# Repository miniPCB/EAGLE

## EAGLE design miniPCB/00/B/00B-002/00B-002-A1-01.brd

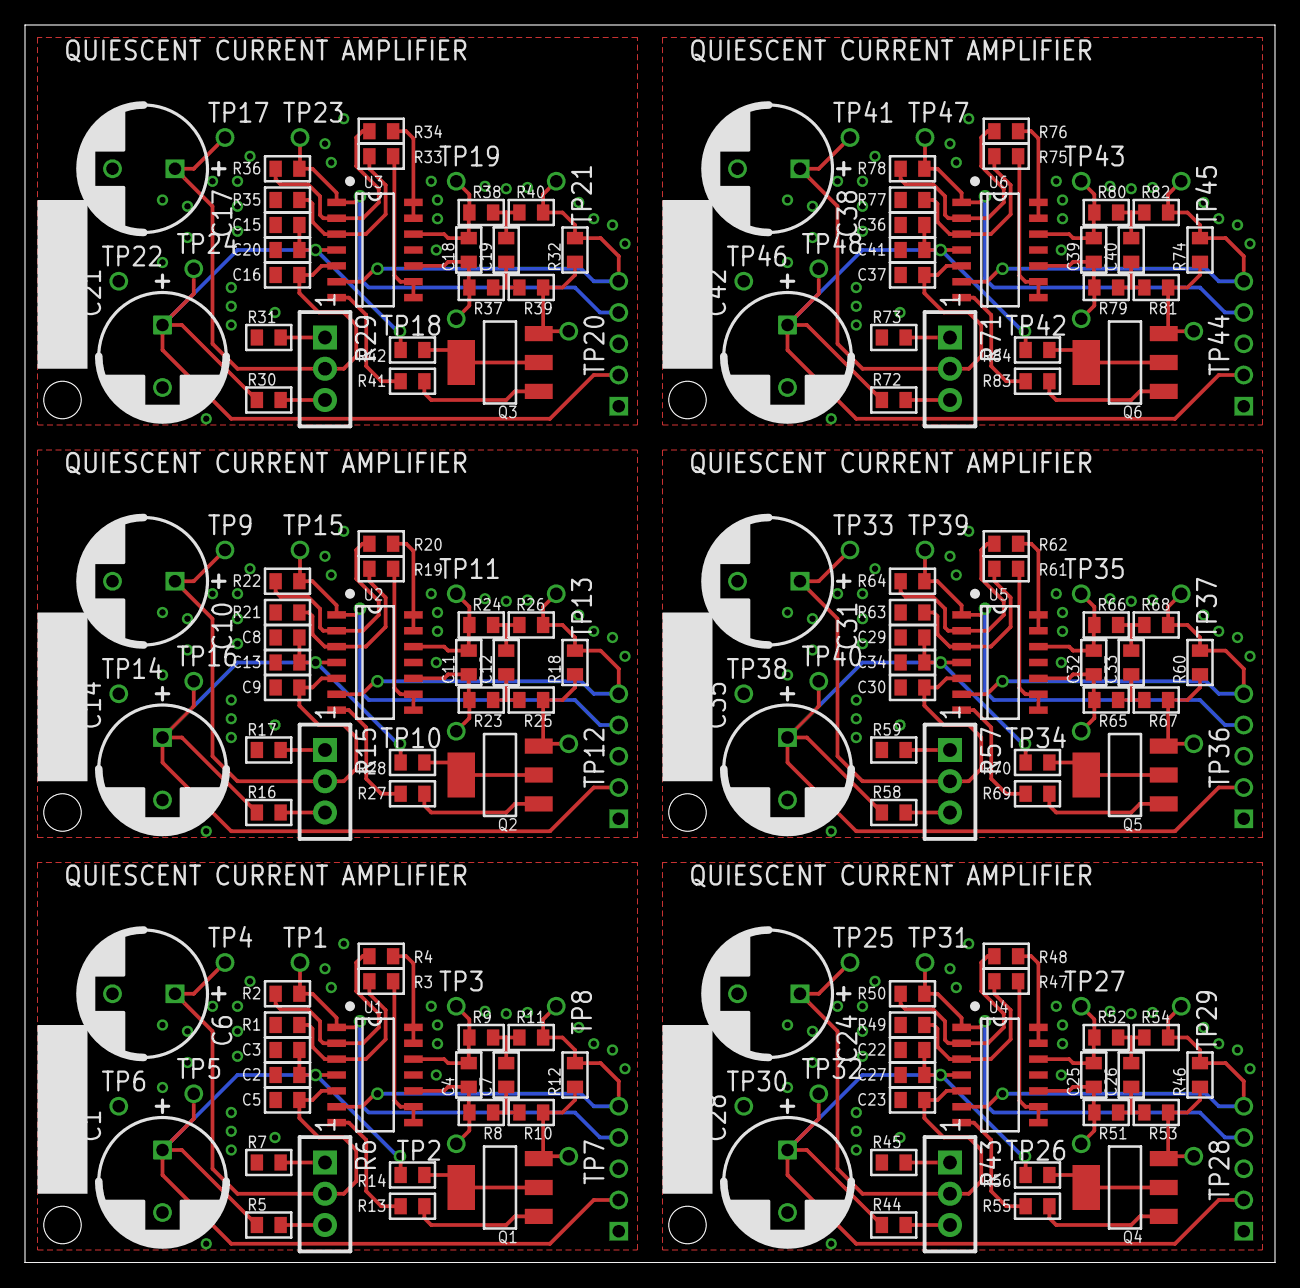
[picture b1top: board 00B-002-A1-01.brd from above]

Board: 2 copper layers, 100.0 x 99.0 mm, 198 parts (0 on the bottom side), 114 nets.

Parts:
C1, C14, C21, C28, C35, C42: 1u; C5MM
C2, C3, C8, C13, C15, C20, C22, C27, C29, C34, C36, C41: 1u; C0805
C4, C5, C7, C9, C11, C12, C16, C18, C19, C23, C25, C26, C30, C32, C33, C37, C39, C40: C0805
C6, C10, C17, C24, C31, C38: C5MM
P1, P2, P3, P4, P5, P6: PINS_1X5
PCB1, PCB2, PCB3, PCB4, PCB5, PCB6: MINIPCB_0P_33X50
Q1, Q2, Q3, Q4, Q5, Q6: SOT223
R1, R2, R3, R4, R5, R7, R8, R9, R10, R11, R12, R13, R14, R16, R17, R18, R19, R20, R21, R22, R23, R24, R25, R26, R27, R28, R30, R31, R32, R33, R34, R35, R36, R37, R38, R39, R40, R41, R42, R44, R45, R46, R47, R48, R49, R50, R51, R52, R53, R54, R55, R56, R58, R59, R60, R61, R62, R63, R64, R65, R66, R67, R68, R69, R70, R72, R73, R74, R75, R76, R77, R78, R79, R80, R81, R82, R83, R84: R0805
R6, R15, R29, R43, R57, R71: TRIM_0100
TP1, TP2, TP3, TP4, TP5, TP6, TP7, TP8, TP9, TP10, TP11, TP12, TP13, TP14, TP15, TP16, TP17, TP18, TP19, TP20, TP21, TP22, TP23, TP24, TP25, TP26, TP27, TP28, TP29, TP30, TP31, TP32, TP33, TP34, TP35, TP36, TP37, TP38, TP39, TP40, TP41, TP42, TP43, TP44, TP45, TP46, TP47, TP48: PINS_1_TESTPOINT_KE5000_NOTEXT
U1, U2, U3, U4, U5, U6: 324; SO14

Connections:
GND: C1.-, C2.2, C3.2, C5.2, C6.-, P1.1, R1.2, R7.1, TP6.1, U1.11
GND1: C8.2, C9.2, C10.-, C13.2, C14.-, P2.1, R17.1, R21.2, TP14.1, U2.11
GND2: C15.2, C16.2, C17.-, C20.2, C21.-, P3.1, R31.1, R35.2, TP22.1, U3.11
GND3: C22.2, C23.2, C24.-, C27.2, C28.-, P4.1, R45.1, R49.2, TP30.1, U4.11
GND4: C29.2, C30.2, C31.-, C34.2, C35.-, P5.1, R59.1, R63.2, TP38.1, U5.11
GND5: C36.2, C37.2, C38.-, C41.2, C42.-, P6.1, R73.1, R77.2, TP46.1, U6.11
ISIGNAL: P1.4, R2.2, TP1.1, U1.1
ISIGNAL1: P2.4, R22.2, TP15.1, U2.1
ISIGNAL2: P3.4, R36.2, TP23.1, U3.1
ISIGNAL3: P4.4, R50.2, TP31.1, U4.1
ISIGNAL4: P5.4, R64.2, TP39.1, U5.1
ISIGNAL5: P6.4, R78.2, TP47.1, U6.1
unnamed: Q1.2, Q1.4.TAB, R14.1
unnamed: R3.1, U1.8, U1.9
unnamed: R4.1, U1.13, U1.14
unnamed: Q1.1, R13.2
unnamed: R6.1, R7.2
unnamed: R5.1, R6.3
unnamed: R13.1, U1.7
unnamed: R2.1, R4.2, U1.2
unnamed: R1.1, R3.2, U1.3
unnamed: R15.1, R17.2
unnamed: R15.3, R16.1
unnamed: R19.1, U2.8, U2.9
unnamed: R20.1, U2.13, U2.14
unnamed: C4.1, R8.2, TP2.1, U1.10
unnamed: C4.2, R9.2, TP3.1, U1.12
unnamed: C7.1, R8.1, R10.2
unnamed: C7.2, R9.1, R11.2
unnamed: R20.2, R22.1, U2.2
unnamed: R19.2, R21.1, U2.3
unnamed: C11.1, R23.2, TP10.1, U2.10
unnamed: C11.2, R24.2, TP11.1, U2.12
unnamed: C12.1, R23.1, R25.2
unnamed: C12.2, R24.1, R26.2
unnamed: Q2.1, R27.2
unnamed: R27.1, U2.7
unnamed: Q2.2, Q2.4.TAB, R28.1
unnamed: R29.1, R31.2
unnamed: R29.3, R30.1
unnamed: R33.1, U3.8, U3.9
unnamed: R34.1, U3.13, U3.14
unnamed: R34.2, R36.1, U3.2
unnamed: R33.2, R35.1, U3.3
unnamed: C18.1, R37.2, TP18.1, U3.10
unnamed: C18.2, R38.2, TP19.1, U3.12
unnamed: C19.1, R37.1, R39.2
unnamed: C19.2, R38.1, R40.2
unnamed: Q3.1, R41.2
unnamed: R41.1, U3.7
unnamed: Q3.2, Q3.4.TAB, R42.1
unnamed: R43.1, R45.2
unnamed: R43.3, R44.1
unnamed: R47.1, U4.8, U4.9
unnamed: R48.1, U4.13, U4.14
unnamed: R48.2, R50.1, U4.2
unnamed: R47.2, R49.1, U4.3
unnamed: C25.1, R51.2, TP26.1, U4.10
unnamed: C25.2, R52.2, TP27.1, U4.12
unnamed: C26.1, R51.1, R53.2
unnamed: C26.2, R52.1, R54.2
unnamed: Q4.1, R55.2
unnamed: R55.1, U4.7
unnamed: Q4.2, Q4.4.TAB, R56.1
unnamed: R57.1, R59.2
unnamed: R57.3, R58.1
unnamed: R61.1, U5.8, U5.9
unnamed: R62.1, U5.13, U5.14
unnamed: R62.2, R64.1, U5.2
unnamed: R61.2, R63.1, U5.3
unnamed: C32.1, R65.2, TP34.1, U5.10
unnamed: C32.2, R66.2, TP35.1, U5.12
unnamed: C33.1, R65.1, R67.2
unnamed: C33.2, R66.1, R68.2
unnamed: Q5.1, R69.2
unnamed: R69.1, U5.7
unnamed: Q5.2, Q5.4.TAB, R70.1
unnamed: R71.1, R73.2
unnamed: R71.3, R72.1
unnamed: R75.1, U6.8, U6.9
unnamed: R76.1, U6.13, U6.14
unnamed: R76.2, R78.1, U6.2
unnamed: R75.2, R77.1, U6.3
unnamed: C39.1, R79.2, TP42.1, U6.10
unnamed: C39.2, R80.2, TP43.1, U6.12
unnamed: C40.1, R79.1, R81.2
unnamed: C40.2, R80.1, R82.2
unnamed: Q6.1, R83.2
unnamed: R83.1, U6.7
unnamed: Q6.2, Q6.4.TAB, R84.1
V+: C1.+, C2.1, C3.1, P1.2, R5.2, R14.2, TP5.1, U1.4
V+1: C8.1, C13.1, C14.+, P2.2, R16.2, R28.2, TP16.1, U2.4
V+2: C15.1, C20.1, C21.+, P3.2, R30.2, R42.2, TP24.1, U3.4
V+3: C22.1, C27.1, C28.+, P4.2, R44.2, R56.2, TP32.1, U4.4
V+4: C29.1, C34.1, C35.+, P5.2, R58.2, R70.2, TP40.1, U5.4
V+5: C36.1, C41.1, C42.+, P6.2, R72.2, R84.2, TP48.1, U6.4
VOUT: P1.5, R11.1, R12.2, TP8.1, U1.6
VOUT1: P2.5, R18.2, R26.1, TP13.1, U2.6
VOUT2: P3.5, R32.2, R40.1, TP21.1, U3.6
VOUT3: P4.5, R46.2, R54.1, TP29.1, U4.6
VOUT4: P5.5, R60.2, R68.1, TP37.1, U5.6
VOUT5: P6.5, R74.2, R82.1, TP45.1, U6.6
VREF: C5.1, C6.+, R6.2, TP4.1, U1.5
VREF1: C9.1, C10.+, R15.2, TP9.1, U2.5
VREF2: C16.1, C17.+, R29.2, TP17.1, U3.5
VREF3: C23.1, C24.+, R43.2, TP25.1, U4.5
VREF4: C30.1, C31.+, R57.2, TP33.1, U5.5
VREF5: C37.1, C38.+, R71.2, TP41.1, U6.5
VSIGAL: Q1.3, R10.1, R12.1, TP7.1
VSIGAL1: Q2.3, R18.1, R25.1, TP12.1
VSIGAL2: Q3.3, R32.1, R39.1, TP20.1
VSIGAL3: Q4.3, R46.1, R53.1, TP28.1
VSIGAL4: Q5.3, R60.1, R67.1, TP36.1
VSIGAL5: Q6.3, R74.1, R81.1, TP44.1

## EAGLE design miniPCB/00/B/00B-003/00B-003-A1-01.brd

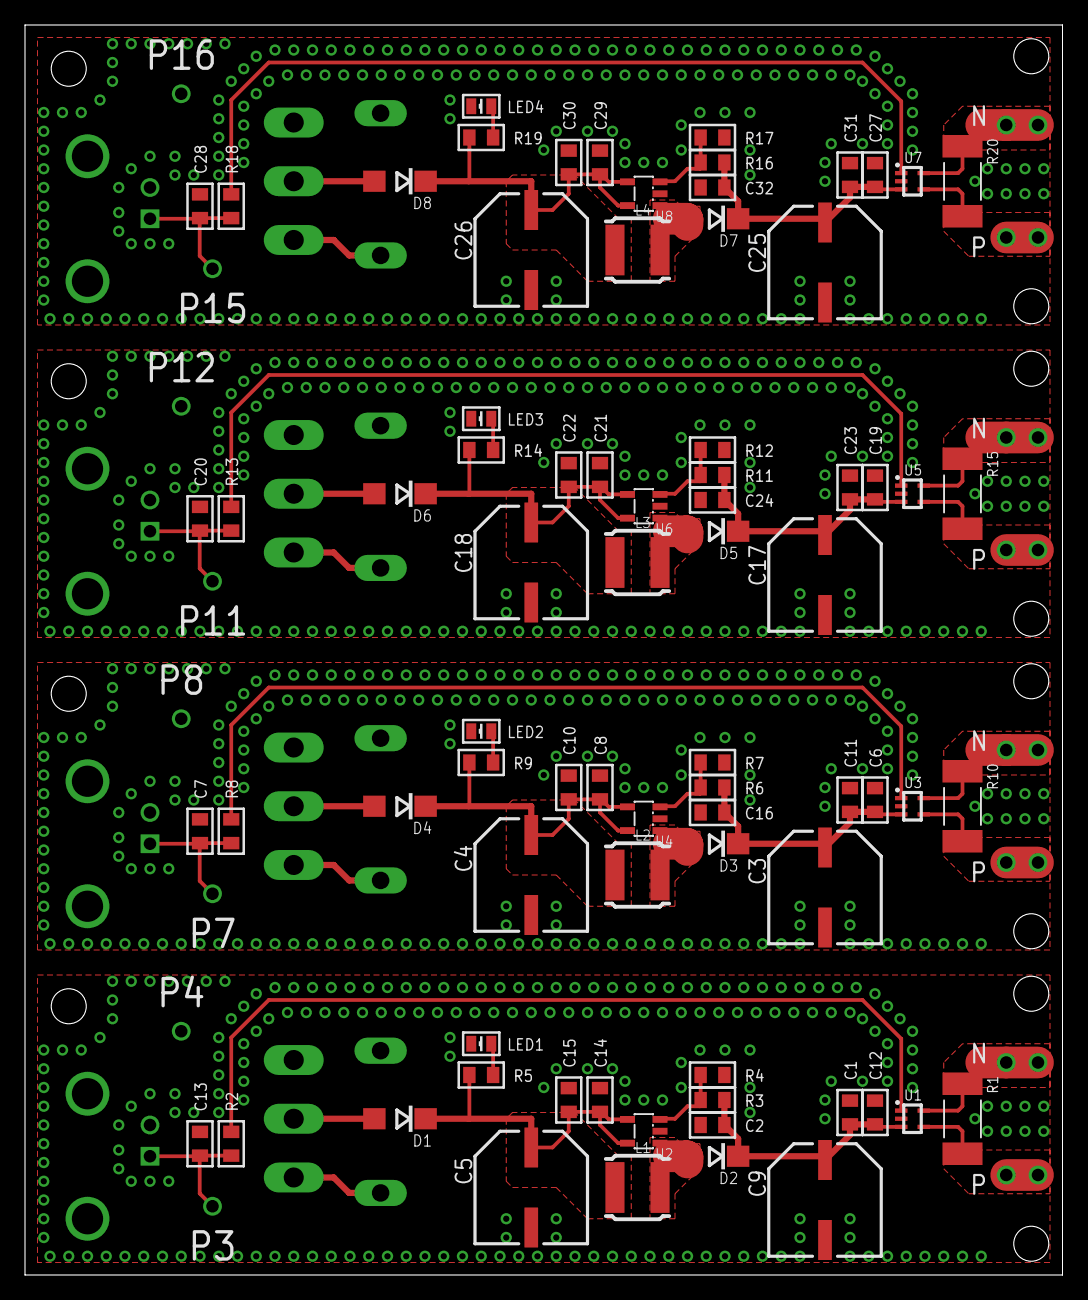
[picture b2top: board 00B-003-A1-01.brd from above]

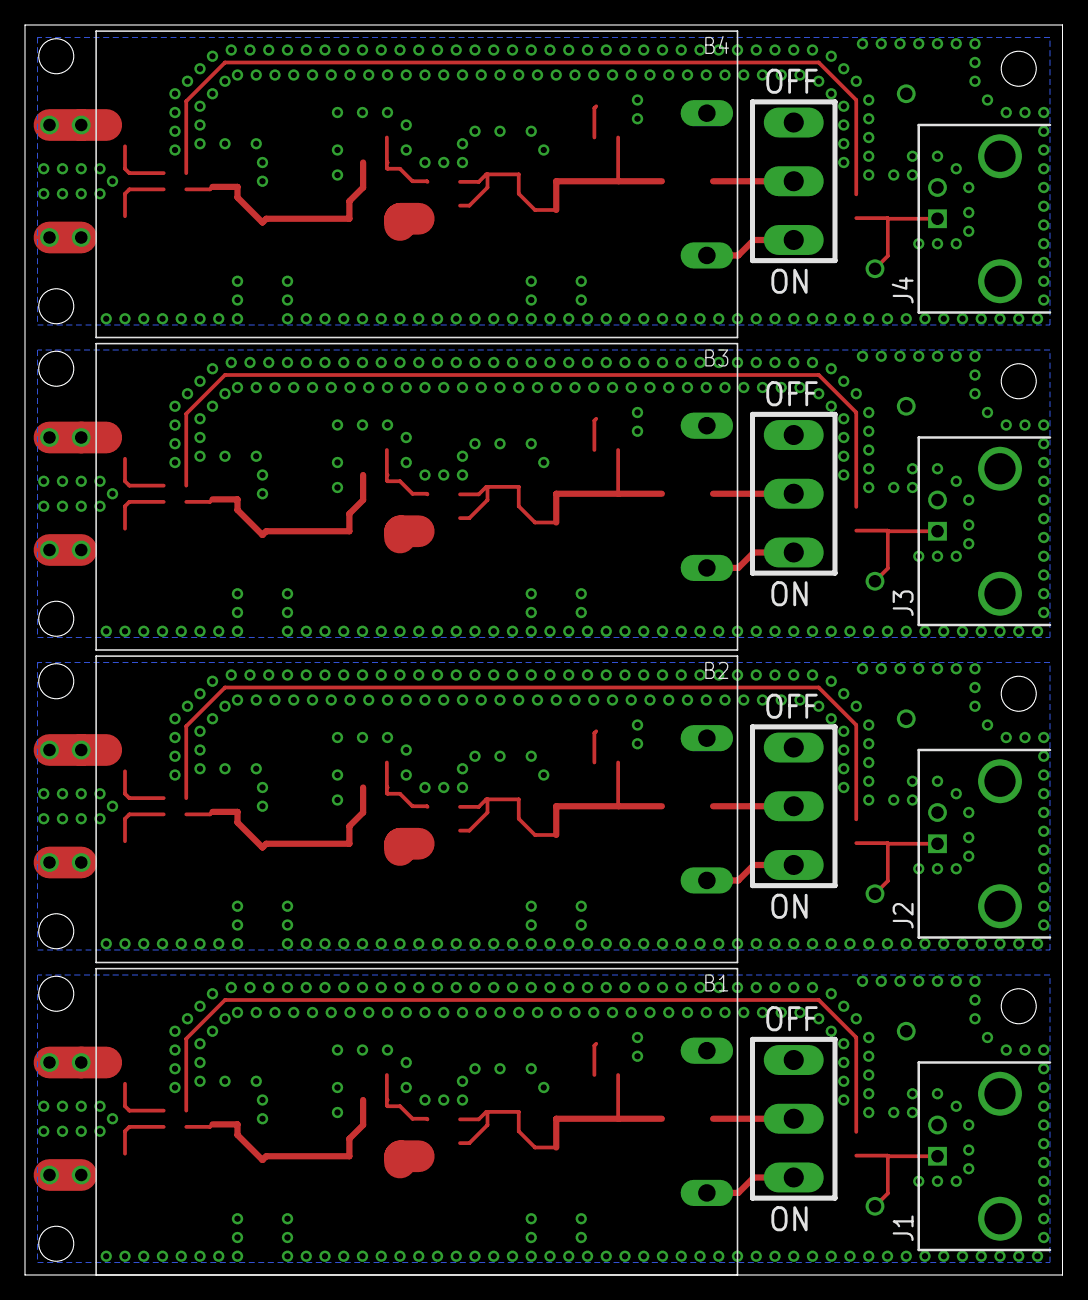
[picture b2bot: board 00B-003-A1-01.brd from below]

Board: 2 copper layers, 83.0 x 100.0 mm, 105 parts (8 on the bottom side), 48 nets.

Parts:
B1, B2, B3, B4: 2 AAA; 2XAAA
C1, C10, C11, C15, C22, C23, C30, C31: 1u; C0805
C2, C16, C24, C32: 100p; C0805
C3, C9, C17, C25: 4u7; C-PCR-8X10
C4, C5, C18, C26: 22u; C-PCR-8X10
C6, C8, C12, C14, C19, C21, C27, C29: 100n; C0805
C7, C13, C20, C28: 1n; C0805
D1, D2, D3, D4, D5, D6, D7, D8: 1N5819; DO214AC
E$1: MINIPCB_PANEL_IMAGEFRAME
J1, J2, J3, J4: BNC_RIGHTANGLE
L1, L2, L3, L4: 10uH; SRN5040
LED1, LED2, LED3, LED4: GREEN; CHIP-LED0805
P1, P2, P5, P6, P9, P10, P13, P14: PINS_1_1MM
P3, P4, P7, P8, P11, P12, P15, P16: PINS_1_TESTPOINT_KE5000
R1, R10, R15, R20: 0R5; R2512K
R2, R5, R8, R9, R13, R14, R18, R19: 250; R0805
R3, R6, R11, R16: 22000; R0805
R4, R7, R12, R17: 1200; R0805
SW1, SW2, SW3, SW4: SWITCH-C&K1001-TEXT
U1, U3, U5, U7: INA290; SC70-5
U2, U4, U6, U8: AP3012; SOT23-5-K

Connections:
B+: C5.+, C14.1ASD, C15.1ASD, D1.C, L1.1, R5.2, U2.4, U2.5
B+1: C4.+, C8.1ASD, C10.1ASD, D4.C, L2.1, R9.2, U4.4, U4.5
B+2: C18.+, C21.1ASD, C22.1ASD, D6.C, L3.1, R14.2, U6.4, U6.5
B+3: C26.+, C29.1ASD, C30.1ASD, D8.C, L4.1, R19.2, U8.4, U8.5
BSW: D1.A, SW1.2
BSW1: D4.A, SW2.2
BSW2: D6.A, SW3.2
BSW3: D8.A, SW4.2
GND: B1.-, C1.2ASDF, C2.2ASDF, C5.-, C9.-, C12.2ASDF, C13.2ASDF, C14.2ASDF, C15.2ASDF, J1.2, LED1.C, P4.1, R4.1, U1.2, U2.2
GND1: B2.-, C3.-, C4.-, C6.2ASDF, C7.2ASDF, C8.2ASDF, C10.2ASDF, C11.2ASDF, C16.2ASDF, J2.2, LED2.C, P8.1, R7.1, U3.2, U4.2
GND2: B3.-, C17.-, C18.-, C19.2ASDF, C20.2ASDF, C21.2ASDF, C22.2ASDF, C23.2ASDF, C24.2ASDF, J3.2, LED3.C, P12.1, R12.1, U5.2, U6.2
GND3: B4.-, C25.-, C26.-, C27.2ASDF, C28.2ASDF, C29.2ASDF, C30.2ASDF, C31.2ASDF, C32.2ASDF, J4.2, LED4.C, P16.1, R17.1, U7.2, U8.2
HV: C1.1ASD, C2.1ASD, C9.+, C12.1ASD, D2.C, R3.2, U1.3
HV1: C3.+, C6.1ASD, C11.1ASD, C16.1ASD, D3.C, R6.2, U3.3
HV2: C17.+, C19.1ASD, C23.1ASD, C24.1ASD, D5.C, R11.2, U5.3
HV3: C25.+, C27.1ASD, C31.1ASD, C32.1ASD, D7.C, R16.2, U7.3
HV_FB: R3.1, R4.2, U2.3
HV_FB1: R6.1, R7.2, U4.3
HV_FB2: R11.1, R12.2, U6.3
HV_FB3: R16.1, R17.2, U8.3
HV_SW: D2.A, L1.2, U2.1
HV_SW1: D3.A, L2.2, U4.1
HV_SW2: D5.A, L3.2, U6.1
HV_SW3: D7.A, L4.2, U8.1
N: P2.1, P2.2, R1.1, U1.5
N1: P6.1, P6.2, R10.1, U3.5
N2: P10.1, P10.2, R15.1, U5.5
N3: P14.1, P14.2, R20.1, U7.5
unnamed: LED1.A, R5.1
unnamed: B2.+, SW2.1
unnamed: LED2.A, R9.1
unnamed: B3.+, SW3.1
unnamed: LED3.A, R14.1
unnamed: B4.+, SW4.1
unnamed: B1.+, SW1.1
unnamed: LED4.A, R19.1
OUTSIGNAL: R2.1, U1.1
OUTSIGNAL1: R8.1, U3.1
OUTSIGNAL2: R13.1, U5.1
OUTSIGNAL3: R18.1, U7.1
P: P1.1, P1.2, R1.2, U1.4
P1: P5.1, P5.2, R10.2, U3.4
P2: P9.1, P9.2, R15.2, U5.4
P3: P13.1, P13.2, R20.2, U7.4
SIGNAL: C13.1ASD, J1.1, P3.1, R2.2
SIGNAL1: C7.1ASD, J2.1, P7.1, R8.2
SIGNAL2: C20.1ASD, J3.1, P11.1, R13.2
SIGNAL3: C28.1ASD, J4.1, P15.1, R18.2

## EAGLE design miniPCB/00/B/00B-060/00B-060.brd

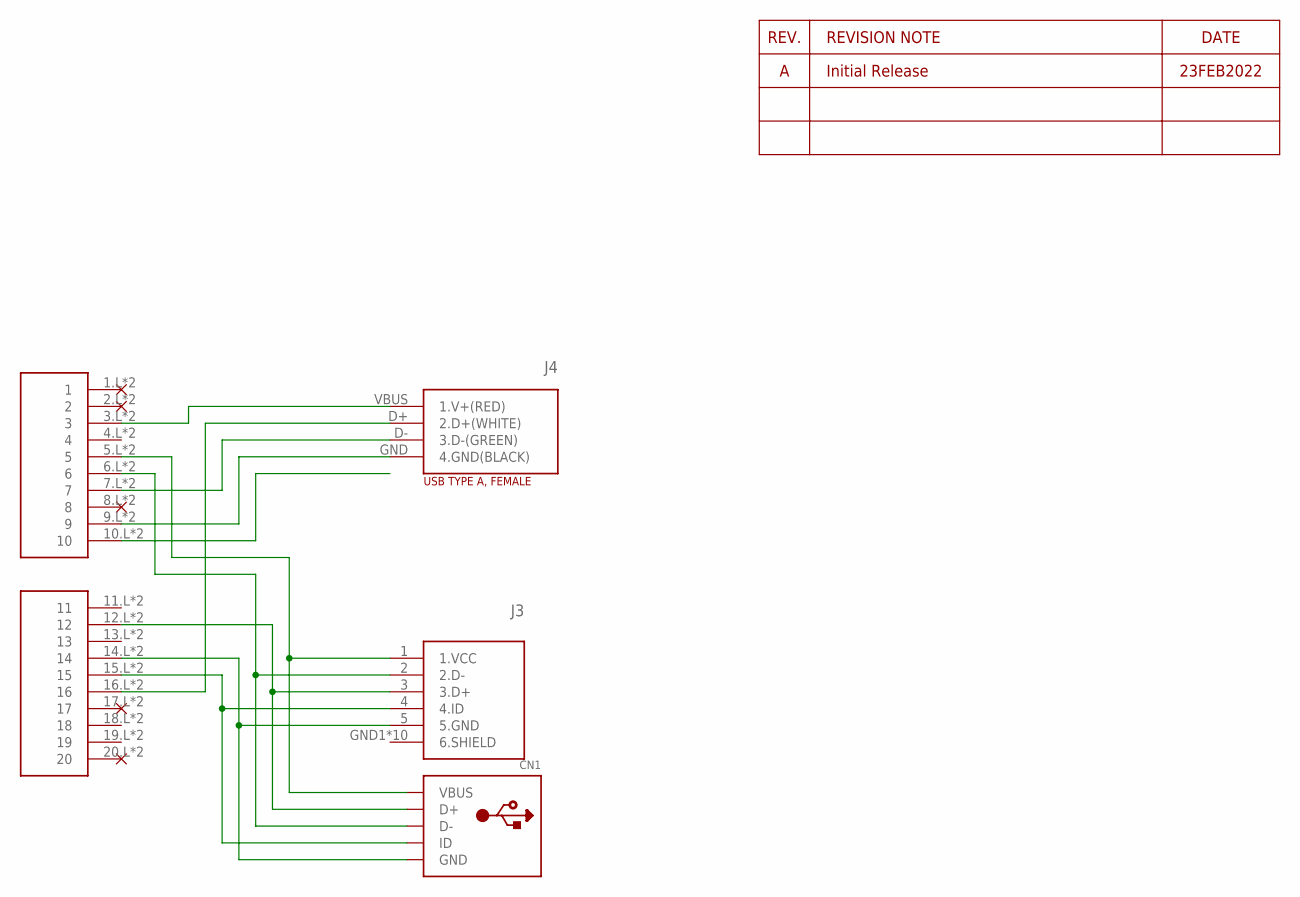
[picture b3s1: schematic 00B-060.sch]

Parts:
CN1: USBMINIB; USB-MINIB
J3: USB; USB_MICRO
J4: USB_A_FEMALE; TYPE-A-FEMALE
U$1: VIVA_PIC16SHIELD; VIVA_SHIELD

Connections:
unnamed: J4.VBUS (1.V+(RED)), U$1.3.L (3), U$1.3.R (3)
unnamed: J4.D+ (2.D+(WHITE)), U$1.16.L (16), U$1.16.R (16)
unnamed: J4.D- (3.D-(GREEN)), U$1.7.L (7), U$1.7.R (7)
unnamed: J4.GND (4.GND(BLACK)), U$1.9.L (9), U$1.9.R (9)
unnamed: U$1.10.L (10), U$1.10.R (10)
unnamed: CN1.VBUS, J3.1 (1.VCC), U$1.5.L (5), U$1.5.R (5)
unnamed: CN1.D+, J3.3 (3.D+), U$1.12.L (12), U$1.12.R (12)
unnamed: CN1.D-, J3.2 (2.D-), U$1.6.L (6), U$1.6.R (6)
unnamed: CN1.GND, J3.5 (5.GND), U$1.14.L (14), U$1.14.R (14)
unnamed: CN1.ID, J3.4 (4.ID), U$1.15.L (15), U$1.15.R (15)

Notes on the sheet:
23FEB2022

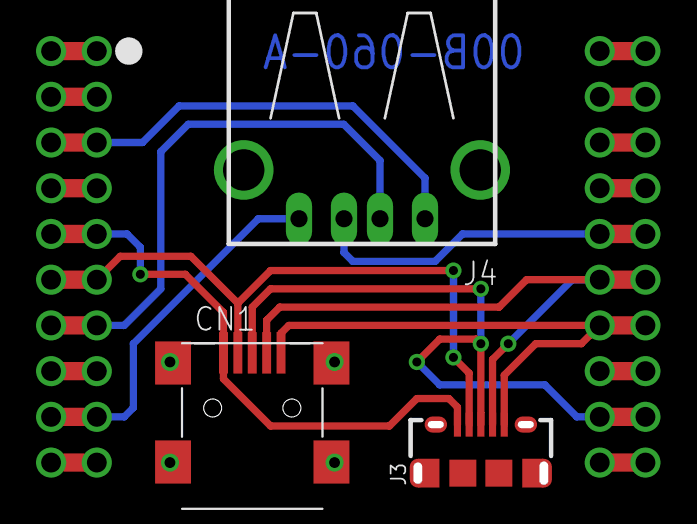
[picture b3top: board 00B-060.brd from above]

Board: 2 copper layers, 4 parts (0 on the bottom side), 10 nets.
